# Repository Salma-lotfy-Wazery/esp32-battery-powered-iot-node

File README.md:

# 📡 ESP32 Battery-Powered IoT Telemetry Node

A compact, reliable, and energy-efficient custom hardware platform engineered for wireless sensor monitoring and remote telemetry applications. Built around the **Espressif ESP32-WROOM-32** module, this node combines precision sensor interfaces, on-board Lithium-Polymer (LiPo) battery charge management, and a modern USB-C interface into a robust 2-layer PCB layout.

---

## 🖼️ 3D Render & Visual Inspection

<p align="center">
  <em>Figure 1: Full 3D assembly render of the ESP32 Battery-Powered IoT Node.</em>
</p>

---

## ⚡ Technical Architecture & Hardware Features

### 1. Power Distribution & Battery Management
- **USB Interface**: USB Type-C receptacle wired for standard 5V VBUS power negotiation and system integration.
- **Battery Charging**: Integrated Single-Cell Li-Ion/LiPo battery management circuit (Linear Constant-Current / Constant-Voltage charging) with charge-status telemetry.
- **Voltage Regulation**: Low-Dropout (LDO) regulator delivering a stable, low-noise 3.3V power rail to ensure radio stability during Wi-Fi/BLE bursts.
- **Power Path & Protection**: Reverse protection and decoupling networks mitigating voltage ripple across analog and digital loads.

### 2. Microcontroller & Sensor Interfaces
- **MCU**: ESP32-WROOM-32 high-performance dual-core 32-bit Tensilica Xtensa LX6 microprocessor operating at up to 240 MHz.
- **Wireless Connectivity**: Integrated 2.4 GHz 802.11 b/g/n Wi-Fi and Bluetooth v4.2 / BLE.
- **Telemetry Bus**: Dedicated I2C bus featuring proper pull-up resistors for multi-sensor interfacing (environmental, motion, and ambient instrumentation).
- **Control & Diagnostics**: Hardware Pushbuttons for system `EN` (Reset) and `IO0` (Bootloader Strap), plus dedicated LED indicators for power and user status.
- **Test Points**: Strategic analog and digital hardware test points for oscilloscope probing and rapid bring-up validation.

---

## 📐 PCB Layout & Documentation

| Isometric 3D Model | Top View / Layout View |
| :---: | :---: |
|  |  |

### PCB Specifications
- **Board Stackup**: 2-Layer FR4 Standard
- **Finished Copper Weight**: 1 oz (35 µm)
- **Ground Strategy**: Continuous, low-impedance ground return planes on both Top and Bottom layers stitched with vias.
- **Mechanical Form Factor**: Designed with 4 corner mounting holes for standard standoffs and protective enclosure mounting.

---
## ⚖️ License

This project is licensed under the CERN Open Hardware Licence Version 2 - Weakly Reciprocal (CERN-OHL-W-2.0). See the [LICENSE](LICENSE) file for more information.

## 📂 Repository File Tree

├── project 1 pcb.kicad_pcb              # Multi-layer PCB routing and layout
├── .gitignore                           # Excludes KiCad temporary, backup & lock files
└── README.md                            # Primary project documentation

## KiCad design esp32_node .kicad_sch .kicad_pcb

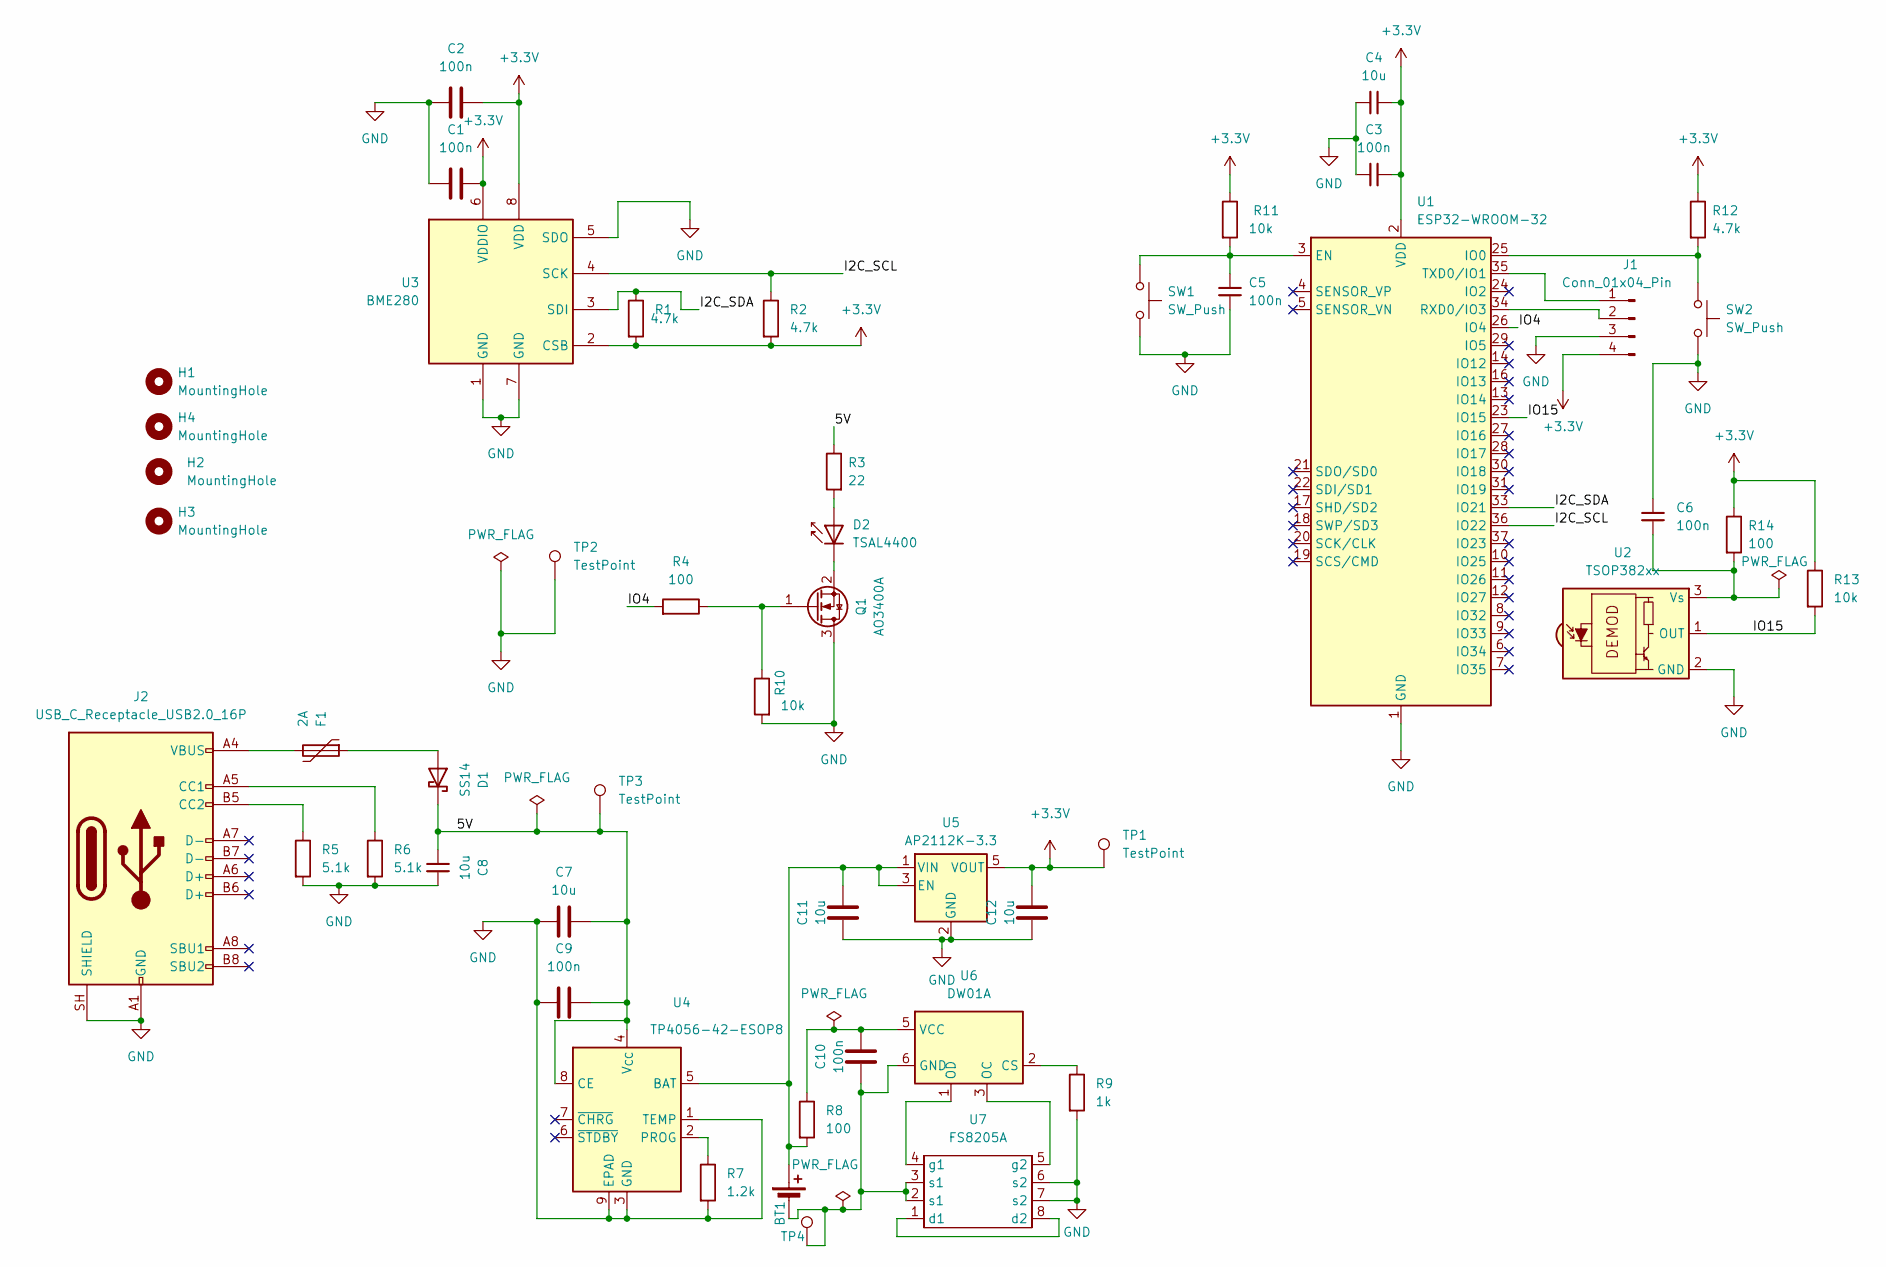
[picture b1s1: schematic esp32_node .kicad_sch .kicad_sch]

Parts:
BT1: Battery_Cell; JST_PH_S2B-PH-K_1x02_P2.00mm_Horizontal
C1, C2, C3, C5, C6, C9, C10: 100n; C_0805_2012Metric
C4, C7, C8, C11, C12: 10u; C_0805_2012Metric
D1: SS14; D_SMA
D2: TSAL4400; LED_D3.0mm_IRBlack
F1: 2A; Fuse_1206_3216Metric
H1, H2, H3, H4: MountingHole; MountingHole_3.2mm_M3
J1: Conn_01x04_Pin; PinHeader_1x04_P2.54mm_Vertical
J2: USB_C_Receptacle_USB2.0_16P; USB_C_Receptacle_HRO_TYPE-C-31-M-12
Q1: AO3400A; SOT-23
R1, R2, R12: 4.7k; R_0805_2012Metric
R3: 22; R_2512_6332Metric
R4, R8, R14: 100; R_0805_2012Metric
R5, R6: 5.1k; R_0805_2012Metric
R7: 1.2k; R_0805_2012Metric
R9: 1k; R_0805_2012Metric
R10, R11, R13: 10k; R_0805_2012Metric
SW1, SW2: SW_Push; SW_Push_1P1T_XKB_TS-1187A
TP1, TP2, TP3, TP4: TestPoint; TestPoint_Pad_D1.5mm
U1: ESP32-WROOM-32; LCSC part C82899
U2: TSOP382xx; Vishay_MINICAST-3Pin
U3: BME280; Bosch_LGA-8_2.5x2.5mm_P0.65mm_ClockwisePinNumbering
U4: TP4056-42-ESOP8; SOIC-8-1EP_3.9x4.9mm_P1.27mm_EP2.29x3mm_ThermalVias
U5: AP2112K-3.3; SOT-23-5
U6: DW01A; SOT-23-6
U7: FS8205A; TSSOP-8_4.4x3mm_P0.65mm

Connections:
+3.3V: C1.2, C2.2, C3.1, C4.1, C12.1, J1.4, R1.2, R2.2, R11.1, R12.1, R13.1, R14.1, TP1.1 (1_1), U1.2 (VDD), U3.2 (CSB), U3.6 (VDDIO), U3.8 (VDD), U5.5 (VOUT)
/5V: C7.2, C8.1, C9.2, D1.1 (K), R3.1, TP3.1 (1_1), U4.4 (V_{CC}), U4.8 (CE)
/I2C_SCL: R2.1, U1.36 (IO22), U3.4 (SCK)
/I2C_SDA: R1.1, U1.33 (IO21), U3.3 (SDI)
/IO4: R4.2, U1.26 (IO4)
/IO15: R13.2, U1.23 (IO15), U2.1 (OUT)
GND: C1.1, C2.1, C3.2, C4.2, C5.1, C6.1, C7.1, C8.2, C9.1, C11.2, C12.2, J1.3, J2.A1 (GND), J2.A12 (GND), J2.B1 (GND), J2.B12 (GND), J2.SH (SHIELD), Q1.3 (D), R5.2, R6.2, R7.2, R9.2, R10.2, SW1.2, SW2.2, TP2.1 (1_1), U1.1 (GND), U1.15 (GND), U1.38 (GND), U1.39 (GND), U2.2 (GND), U3.1 (GND), U3.5 (SDO), U3.7 (GND), U4.1 (TEMP), U4.3 (GND), U4.9 (EPAD), U5.2 (GND), U7.6 (s2), U7.7 (s2)
unnamed: BT1.1 (+), C11.1, R8.2, U4.5 (BAT), U5.1 (VIN), U5.3 (EN)
unnamed: BT1.2 (-), C10.2, TP4.1 (1_1), U6.6 (GND), U7.2 (s1), U7.3 (s1)
unnamed: D1.2 (A), F1.1
unnamed: D2.2 (A), R3.2
unnamed: D2.1 (K), Q1.2 (S)
unnamed: F1.2, J2.A4 (VBUS), J2.A9 (VBUS), J2.B4 (VBUS), J2.B9 (VBUS)
unnamed: J1.1, U1.35 (TXD0/IO1)
unnamed: J1.2, U1.34 (RXD0/IO3)
unnamed: J2.A5 (CC1), R6.1
unnamed: J2.B5 (CC2), R5.1
unnamed: Q1.1 (G), R4.1, R10.1
unnamed: C5.2, R11.2, SW1.1, U1.3 (EN)
unnamed: R12.2, SW2.1, U1.25 (IO0)
unnamed: C6.2, R14.2, U2.3 (Vs)
unnamed: R7.1, U4.2 (PROG)
unnamed: R9.1, U6.2 (CS)
unnamed: U6.3 (OC), U7.5 (g2)
unnamed: U6.1 (OD), U7.4 (g1)
unnamed: C10.1, R8.1, U6.5 (VCC)
unnamed: U7.1 (d1), U7.8 (d2)

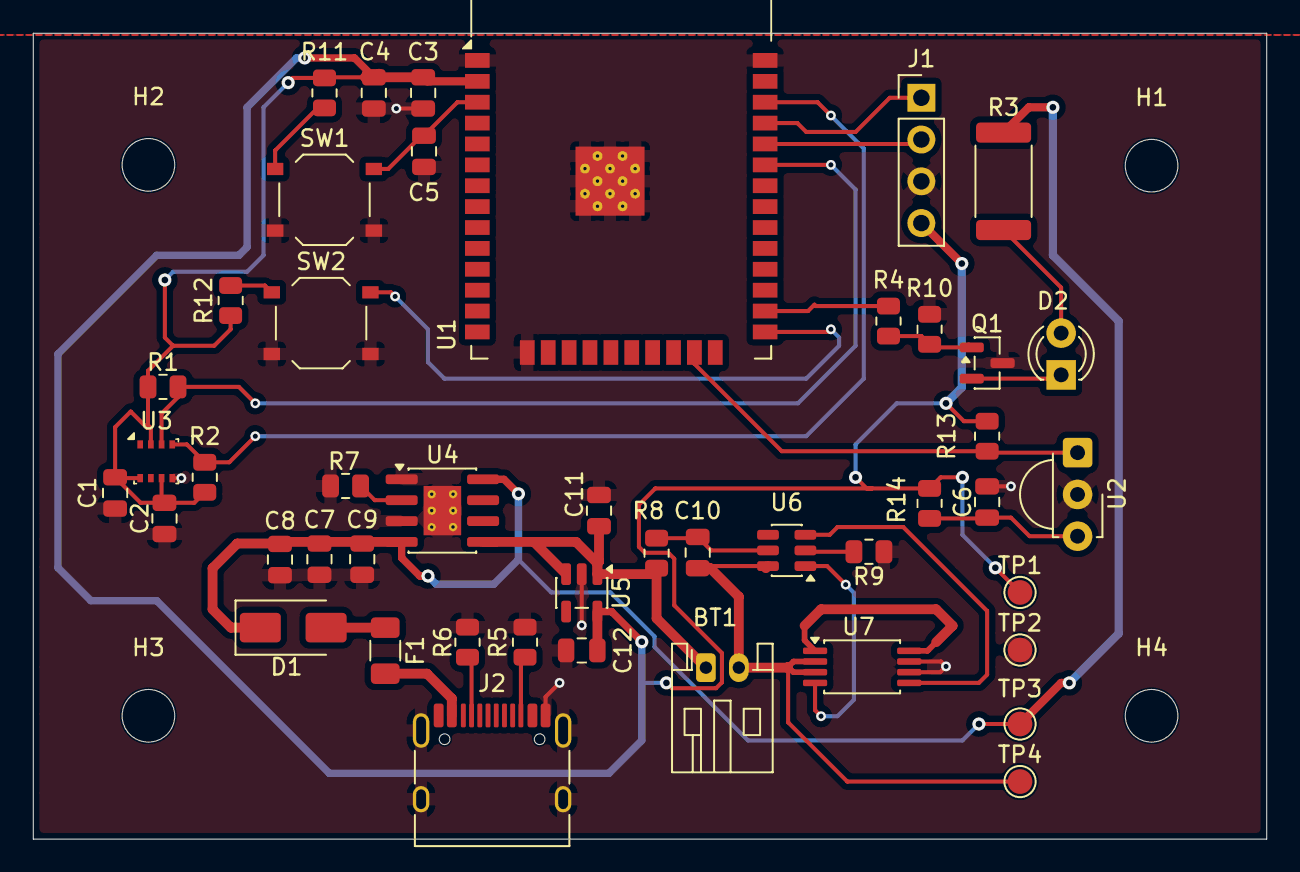
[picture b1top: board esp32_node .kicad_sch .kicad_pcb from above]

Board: 2 copper layers, 75.0 x 49.0 mm, 50 parts (0 on the bottom side), 27 nets.

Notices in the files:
README.md:
License: CERN-OHL-P
